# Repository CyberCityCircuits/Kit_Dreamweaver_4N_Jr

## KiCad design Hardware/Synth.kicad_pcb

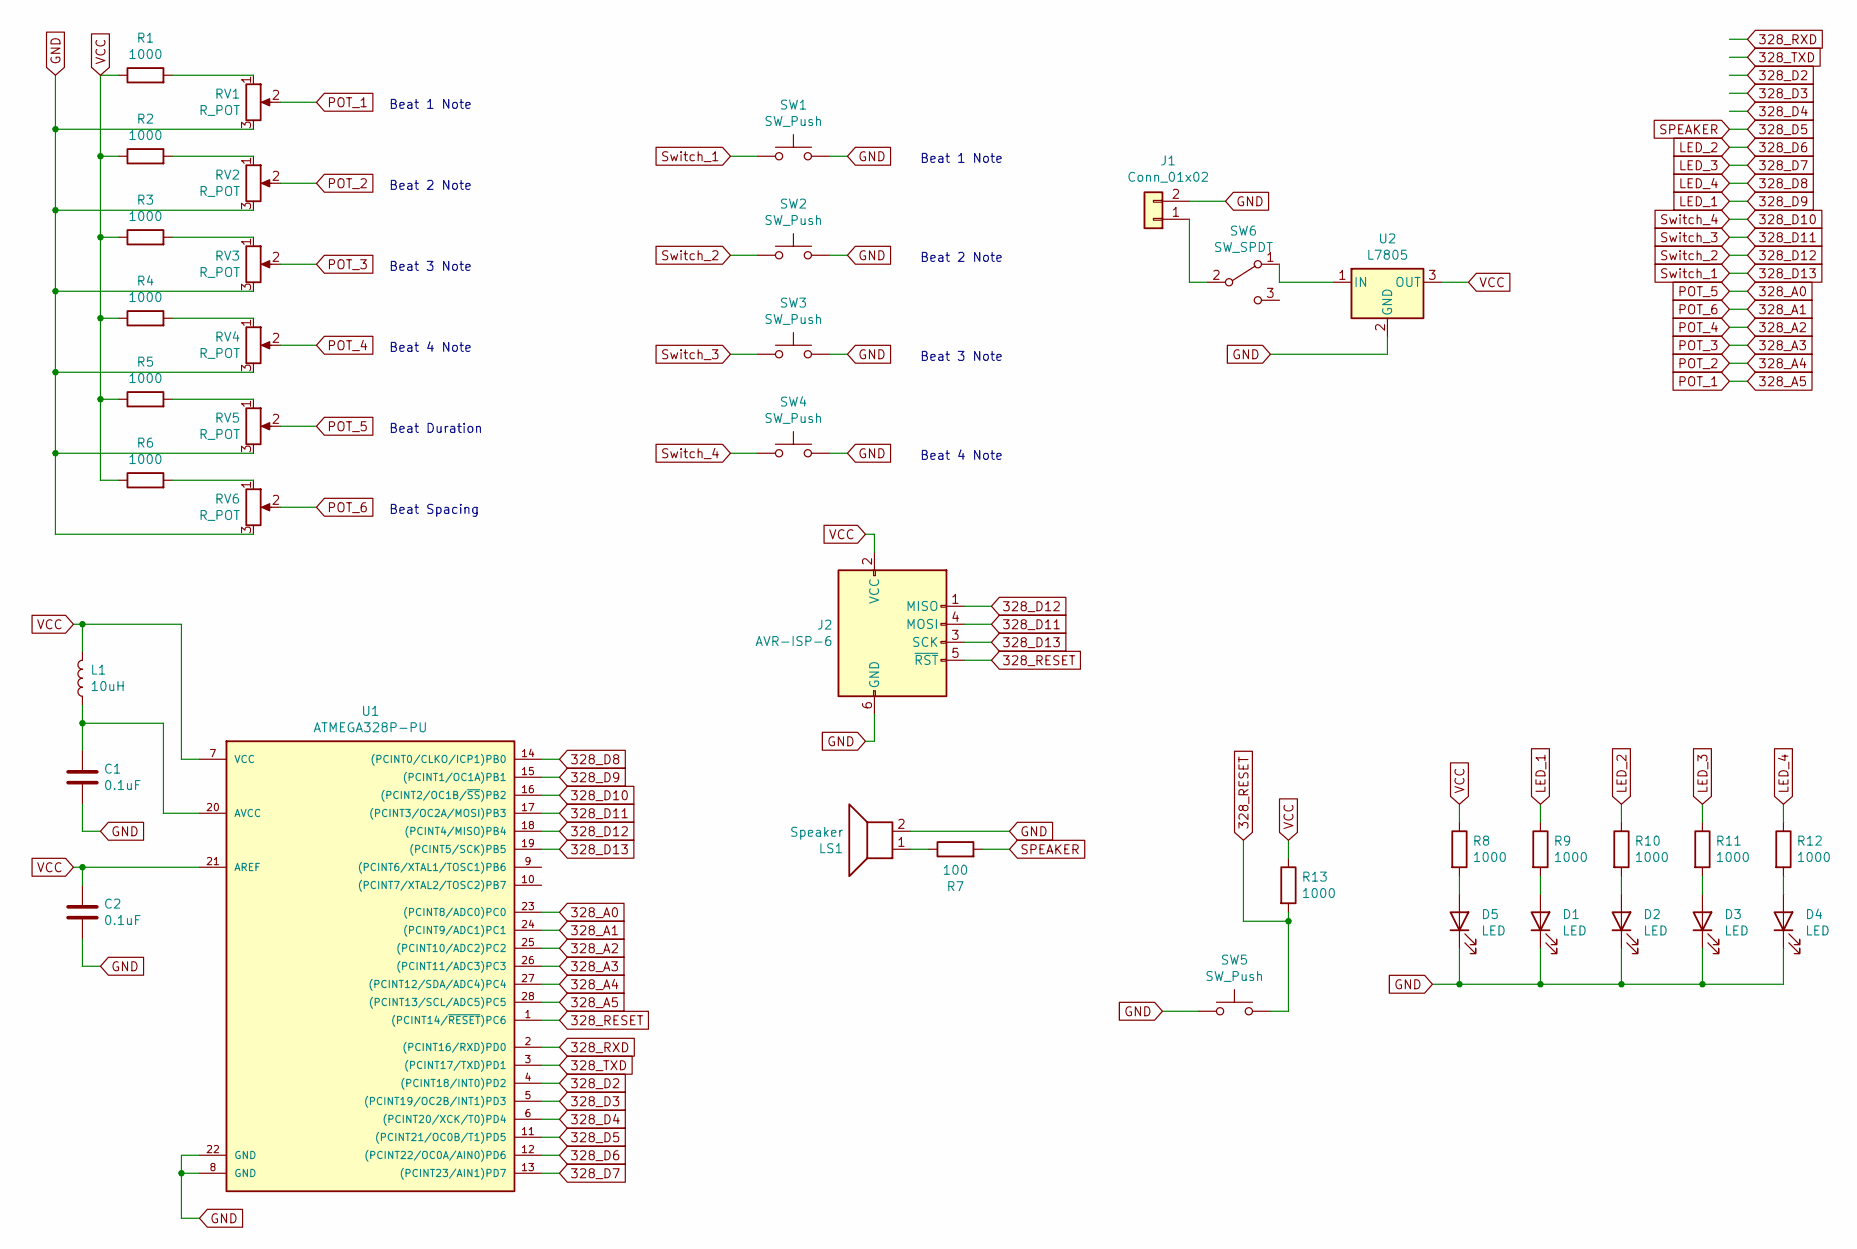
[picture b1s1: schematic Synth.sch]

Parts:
C1, C2: 0.1uF; Schematic - Capacitor 5.0mm
D1, D2, D3, D4, D5: LED; Schematic - LED 5mm(2.56P) 003
J1: Conn_01x02; 9V_Battery_Terminal
J2: AVR-ISP-6; PinSocket_2x03_P2.54mm_Vertical
L1: 10uH; Schematic - Inductor 10.16mm
LS1: Speaker; Speaker_Large_Fuet
R1, R2, R3, R4, R5, R6, R8, R9, R10, R11, R12, R13: 1000; Schematic - Resistor 7.62mm
R7: 100; Schematic - Resistor 7.62mm
RV1, RV2, RV3, RV4, RV5, RV6: R_POT; Potentiometer_Alps_RK09L_Single_Vertical
SW1, SW2, SW3, SW4: SW_Push; Schematic_-_Button_Labeled
SW5: SW_Push; Schematic - Push Button 6.5x4.5
SW6: SW_SPDT; PinHeader_1x03_P2.54mm_Vertical
U1: ATMEGA328P-PU; Schematic - ATMEGA328P-PU
U2: L7805; MOSFET_TO-220-3_Horizontal_TabDown

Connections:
328_A0: RV5.2, U1.23 ((PCINT8/ADC0)PC0)
328_A1: RV6.2, U1.24 ((PCINT9/ADC1)PC1)
328_A2: RV4.2, U1.25 ((PCINT10/ADC2)PC2)
328_A3: RV3.2, U1.26 ((PCINT11/ADC3)PC3)
328_A4: RV2.2, U1.27 ((PCINT12/SDA/ADC4)PC4)
328_A5: RV1.2, U1.28 ((PCINT13/SCL/ADC5)PC5)
328_D2: U1.4 ((PCINT18/INT0)PD2)
328_D3: U1.5 ((PCINT19/OC2B/INT1)PD3)
328_D4: U1.6 ((PCINT20/XCK/T0)PD4)
328_D5: R7.2, U1.11 ((PCINT21/OC0B/T1)PD5)
328_D6: R10.1, U1.12 ((PCINT22/OC0A/AIN0)PD6)
328_D7: R11.1, U1.13 ((PCINT23/AIN1)PD7)
328_D8: R12.1, U1.14 ((PCINT0/CLKO/ICP1)PB0)
328_D9: R9.1, U1.15 ((PCINT1/OC1A)PB1)
328_D10: SW4.1, U1.16 ((PCINT2/OC1B/~SS~)PB2)
328_D11: J2.4 (MOSI), SW3.1, U1.17 ((PCINT3/OC2A/MOSI)PB3)
328_D12: J2.1 (MISO), SW2.1, U1.18 ((PCINT4/MISO)PB4)
328_D13: J2.3 (SCK), SW1.1, U1.19 ((PCINT5/SCK)PB5)
328_RESET: J2.5 (~RST), R13.2, SW5.2, U1.1 ((PCINT14/~RESET~)PC6)
328_RXD: U1.2 ((PCINT16/RXD)PD0)
328_TXD: U1.3 ((PCINT17/TXD)PD1)
GND: C1.2, C2.2, D1.1 (K), D2.1 (K), D3.1 (K), D4.1 (K), D5.1 (K), J1.2, J2.6 (GND), LS1.2, RV1.3, RV2.3, RV3.3, RV4.3, RV5.3, RV6.3, SW1.2, SW2.2, SW3.2, SW4.2, SW5.1, U1.8 (GND), U1.22 (GND), U2.2 (GND)
unnamed: C1.1, L1.1, U1.20 (AVCC)
unnamed: D1.2 (A), R9.2
unnamed: D2.2 (A), R10.2
unnamed: D3.2 (A), R11.2
unnamed: D4.2 (A), R12.2
unnamed: D5.2 (A), R8.2
unnamed: J1.1, SW6.2 (B)
unnamed: LS1.1, R7.1
unnamed: R1.2, RV1.1
unnamed: R2.2, RV2.1
unnamed: R3.2, RV3.1
unnamed: R4.2, RV4.1
unnamed: R5.2, RV5.1
unnamed: R6.2, RV6.1
unnamed: SW6.1 (A), U2.1 (IN)
VCC: C2.1, J2.2 (VCC), L1.2, R1.1, R2.1, R3.1, R4.1, R5.1, R6.1, R8.1, R13.1, U1.7 (VCC), U1.21 (AREF), U2.3 (OUT)

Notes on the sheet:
Beat 1 Note
Beat 2 Note
Beat 3 Note
Beat 4 Note
Beat Spacing
Beat Duration

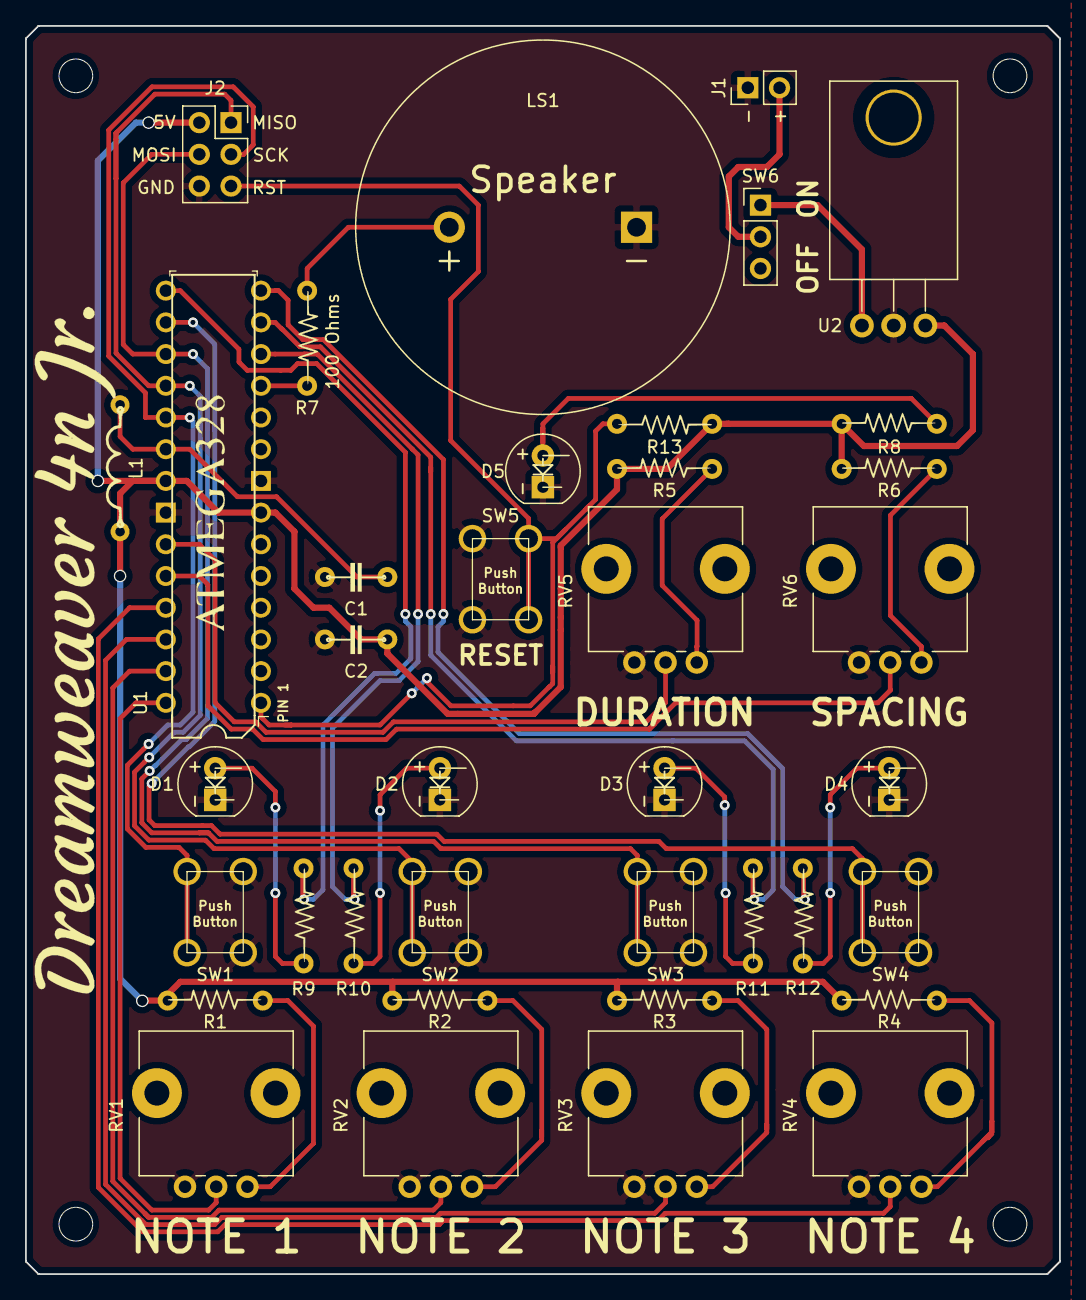
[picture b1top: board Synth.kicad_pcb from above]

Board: 2 copper layers, 82.8 x 100.0 mm, 38 parts (0 on the bottom side), 33 nets.

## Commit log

2021-06-16 Added PDF Copy of Schematic
